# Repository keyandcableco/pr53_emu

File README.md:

# pr53_emu

A replacement display for a Technics SX-PR53 digital piano whose chip-on-glass
LCD died. A tap board sits on the HD44780 bus between the piano's CPU and the
dead display: it mirrors every write, answers the CPU's reads so it never
stalls, logs everything over USB, and forwards each write to a second board
that draws the piano's display on a 3.5" colour TFT. Python tools render the
same display on a laptop and were used to reverse-engineer the glass.

The technique generalizes to most HD44780-compatible LCDs. See
[the writeup](https://keyandcable.com/blog/reviving-the-technics-sx-pr53.html)
for the story and the reasoning behind the design.

```
piano CPU ── HD44780 bus (CN1) ──► carrier J1 ─ level shifters ─► tap (RP2350-Zero) ── USB log ──► tools/
                                                                    │ UART 1 Mbaud
                                                                    ▼
                                                     display (Pico 2) ── 16-bit parallel ──► 3.5" TFT
```

## Status (2026-10-31)

- **Working end to end on the piano.** The carrier board carries both
  RP2350s; the TFT draws the PR53 layout and shows the piano's text.
- **Decoded:** the text lines, tempo, chord root with its flat/sharp,
  transpose, all eight part meters and numbers (hundreds included), and the
  menu page and item readouts with MENU, PAGE, the PAGE arrows and the
  part pointers.
- **Not decoded yet:** chord types and many
  of the shaped labels on the glass (MIDI and more).
  [`docs/front-panel.md`](docs/front-panel.md) tracks the front-panel decode.
- **Carrier v2 works, with one change when you build it:** fit J2 on the
  underside of the board. DB7's pull-down is too weak to do its job on its
  own; the next revision should fix that. Details in
  [`hardware/carrier/README.md`](hardware/carrier/README.md).

## What's in here

| Path | What |
|---|---|
| [`firmware/tap/`](firmware/tap/) | Tap firmware (v18) for the RP2350-Zero: capture, read responses, USB log, display link |
| [`firmware/display/`](firmware/display/) | Display firmware for the Pico 2: decoders, renderer, panel driver, host test |
| [`tools/`](tools/) | Python: live display mock, recorder, offline analyzer, segment-mapping tools |
| [`captures/`](captures/) | Bus recordings from the piano, including the host test's ground-truth frame |
| [`hardware/carrier/`](hardware/carrier/) | The PR53 carrier v2 board: KiCad, generator scripts, Gerbers, bring-up notes (`rev1/` is the first fab) |
| [`hardware/archive/`](hardware/archive/) | Earlier perfboard maps and board plans |
| [`docs/piano-interface.md`](docs/piano-interface.md) | The piano side: CN1 pinout, the bus, busy flag, power |
| [`docs/front-panel.md`](docs/front-panel.md) | Every panel control and display field, decode status, service test modes |

## Build

Needs the [Pico SDK](https://github.com/raspberrypi/pico-sdk) (built with
2.3.0), `arm-none-eabi-gcc`, `cmake` and `make`. Both firmwares find the SDK
through `firmware/pico_sdk_import.cmake`, from `PICO_SDK_PATH` in the
environment or `-DPICO_SDK_PATH=...`.

```bash
export PICO_SDK_PATH=$HOME/pico-sdk
cmake -S firmware/tap     -B build/tap     -DPICO_BOARD=pico2 && make -C build/tap -j
cmake -S firmware/display -B build/display -DPICO_BOARD=pico2 && make -C build/display -j
make -C firmware/display -f host.mk test     # decoder test on the PC, no hardware
```

That gives `build/tap/pr53_emu.uf2` (for the Zero) and
`build/display/pr53_fw.uf2` (for the Pico 2).

## Flash

Hold BOOT (Zero) or BOOTSEL (Pico 2) while plugging in USB, then copy the UF2
onto the RP2350 drive that appears. Power the TFT and the display Pico
together: the display firmware sets up the panel once, at boot.

To check what's already on a board without changing it, use
`picotool verify -f <uf2>` with a picotool built with USB support (see
`hardware/carrier/README.md`, Bring-up).

## Laptop display

```bash
pip install pyserial
python3 tools/pr53_display.py
```

It auto-detects the tap's serial port (override with `--port /dev/ttyACM0` or
`--port COM3`). Power on the piano and you'll see the voice and rhythm names,
the current menu, the raw DDRAM, and a status bar with the event count. If the
log shows `# WARN dropped N events`, the tap's ring buffer overflowed; healthy
runs keep `ring_depth` near 0 on the `# ALIVE` lines. See
[`tools/README.md`](tools/README.md) for the other tools.

## Generalizing to other devices

This trick works on essentially any HD44780-compatible LCD. If you have a piece of vintage gear (synth, drum machine, industrial equipment, arcade board) with a dead text display and the CPU still runs, the same approach applies:

1. Wire the RP2350 to RS, R/W, CS, and DB4-DB7 (through level shifters if the bus is 5 V).
2. Add a pull-down on DB7.
3. Adjust `pio_read_response_init` timing if your target CPU's bus is faster than the SX-PR53's.
4. Rebuild the Python display's LCD dimensions if it's not 16x2.

The state machine and event log format are display-agnostic. The only Technics-specific behavior is the persistent-state heuristic in `pr53_display.py`, which classifies text as menu-label vs voice/rhythm name — easy to strip out or replace.

If you adapt this to another device I'd love to hear about it.

---

## Acknowledgments

Substantial pair-programming with [Claude Opus 4.7](https://www.anthropic.com/claude). The physical work — probing, cutting, wiring, verifying — was mine; the C firmware, the Python tools, the electrical debugging plans, and most of the pattern-matching on byte-level corruption came out of that collaboration. Neither side could have done it alone.

## Related

- [The Key & Cable Company](https://keyandcable.com) — the shop
- [openchord-project](https://github.com/keyandcableco/openchord-project) — earlier RP2350-based restoration for the Suzuki Omnichord OM-27
- [Full writeup](https://keyandcable.com/blog/reviving-the-technics-sx-pr53.html)

## License

MIT. See [LICENSE](LICENSE).

`firmware/pico_sdk_import.cmake` is from the Raspberry Pi Pico SDK and keeps its BSD-3-Clause licence (see the file header).

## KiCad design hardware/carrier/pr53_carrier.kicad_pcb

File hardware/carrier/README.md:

# PR53 Carrier Board (v2)

A 100 x 62 mm 2-layer board that carries the existing two-module build,
socketed on 2.54 mm headers:

    J1 piano in ──► U1/U2 BSS138 shifters ──► A1 RP2350-Zero (tap)
                                                   │ GP8 → GP21 link
                                                   ▼
                              J2 LCD out ◄── A2 Pico 2 (display)

**Status (v2): built and working** (first power-up 2026-10-31, on USB
power). J2 has to be fitted on the underside; see Bring-up below. Routed, DRC 0 errors / 0 unconnected (2
silkscreen-at-edge warnings on A2, same as v1), Gerbers in `gerbers/` and
`pr53_carrier_jlcpcb.zip`. Both module footprints are verified (table below).

**v1 (fabbed 2026-10) has the wrong shifter footprint.** Its rows are 12.70 mm
apart instead of 10.16 mm, and power and GND are swapped on both sides. A
shifter plugged straight into a v1 board is reverse-powered, so jumper LV,
HV and GND by hand. v1 files are kept in `rev1/`.

The back silkscreen carries the maker's mark (The Key & Cable Co. /
keyandcable.com / Technics PR53 Carrier Board) and a QR code to
https://keyandcable.com, drawn as vector squares from
`keyandcable_qr.txt` (0.48 mm modules, 12 mm). It sits between the
Pico's pin rows, inside a via-free zone so no drill hole lands in it.

## Module dimensions

| Module | Value | Source | Constant in `gen_footprints.py` |
|---|---|---|---|
| RP2350-Zero: long edge to long edge, pin centres | 15.24 mm (6 holes) | test-fitted on a v1 board | `ZERO_COL_SPACING` |
| BSS138 4-ch module: HV row to LV row | 10.16 mm (4 holes) | SparkFun's `.brd` | `SHIFTER_ROW_SPACING` |

Shifter pin order, module top view, HV row on the left and LV row on the
right, top to bottom: `HV4 HV3 GND HV HV2 HV1` and `LV4 LV3 GND LV LV2 LV1`.
Taken from SparkFun BOB-12009's own board file
(github.com/sparkfun/Logic_Level_Bidirectional, `Hardware/*.brd`), which the
cheap clones copy.

## Ordering (JLCPCB or similar)

Upload `pr53_carrier_jlcpcb.zip`. 2 layers, 1.6 mm, everything else default.
All traces are ≥ 0.25 mm, vias 0.7/0.35 mm, so nothing needs the expensive options.

## BOM (all through-hole, hand-solder)

| Ref | Part | Note |
|---|---|---|
| A1 | Waveshare RP2350-Zero + 2x 1x9 headers | USB-C at the bottom edge |
| A2 | Raspberry Pi Pico 2 + 2x 1x20 headers | USB at the bottom edge |
| U1, U2 | BSS138 4-ch level shifter module + 2x 1x6 headers each | |
| J1 | 9-pos 3.5 mm screw terminal (Phoenix PT 1,5/9-3.5-H, or 3+3+3 cheap KF350 blocks) | wire openings face the board edge |
| J2 | 2x18 2.54 mm male header | IDC ribbon → panel, pin 1 marked. **Fit it on the underside** (see Bring-up) |
| R1 | 10k axial | **DB7 busy-flag pulldown, needed for the board to work** |
| R2 | 1k axial | power LED |
| D1, D2 | 1N5819 Schottky | 5V into each module (blocks USB back-feed) |
| D3 | 3 mm LED | power |
| C1 | 100 µF 10 V radial, 2.5 mm pitch | |
| C2 | 100 nF ceramic, 5 mm pitch | |

Sockets (female headers) instead of soldering the modules down are a good idea.
The footprints are plain 2.54 mm holes, so either works.

## Wiring (matches the firmware exactly)

**J1, piano in, top to bottom:** GND, +5V, CS, RW, RS, DB7, DB6, DB5, DB4

| Piano | Shifter | Zero |
|---|---|---|
| DB4 | U1 ch1 | GP0 |
| DB5 | U1 ch2 | GP1 |
| DB6 | U1 ch3 | GP2 |
| DB7 (+R1 10k to GND, 5V side) | U1 ch4 | GP3 |
| RS | U2 ch2 | GP4 |
| RW | U2 ch3 | GP5 |
| CS | U2 ch4 | GP7 |
| — | — | GP8 → Pico GP21 (UART link) |

Channels are assigned in the module's own top-to-bottom order, so the
lines run straight across with no crossings. U2 ch1 is spare.

**Shifters are bidirectional on purpose.** The tap firmware answers the
piano's read cycles on DB4-7 (PIO1 in `firmware/tap/src/pr53_emu.c`). A one-way
buffer such as the 74LVC245 in `../archive/KICAD_NETLIST.md` would break that.

**J2, LCD out:** numbered 1:1 with the HiLetgo 36-pin header (straight-through
ribbon). Pico GP0-15 → DB0-15, GP16 RS, GP17 WR, GP18 RST, CS (pin 21) tied
to GND, 5V on pins 1-2, GND on 35-36.

**Power:** one +5V rail from the piano (J1). It feeds the shifter HV sides
and the LCD directly, and each module through its own Schottky (Zero 5V pin,
Pico VSYS). You can plug USB into either module for reflashing while the
piano is on. The shifter LV side runs from the Zero's 3V3 pin, which is the
same rail as the GPIOs it talks to.

## Rebuilding

Everything is generated, so edit the scripts rather than the board:

```bash
/usr/bin/python3 gen_footprints.py      # pr53.pretty (Zero + shifter footprints)
/usr/bin/python3 gen_board.py           # placement, nets, rules, pours (unrouted)
/usr/bin/python3 route.py freerouting-1.9.0.jar   # autoroute + GND stitching (~1 min)
kicad-cli pcb drc pr53_carrier.kicad_pcb
```

Then re-export the Gerbers (or File → Fabrication Outputs in KiCad).
Freerouting 1.9.0 is the last release that runs on Java 17:
https://github.com/freerouting/freerouting/releases/tag/v1.9.0

Use KiCad's own python (`/usr/bin/python3`), the one that can `import pcbnew`.
Re-running `gen_board.py` discards the routing, so route last. Hand edits in
KiCad are fine once you stop regenerating.

## Bring-up (2026-10-31)

First power-up on the piano. The whole chain works: the piano's LCD writes
reach the tap, cross the GP8 → GP21 link, and the display Pico draws them on
the HiLetgo panel. What it took:

- **J2 goes on the underside.** The panel's 36-pin header comes out of its
  back, so a standard 2x18 IDC ribbon from a top-side J2 lands each odd pin on
  its even neighbour. Power survives (pins 1/2 are both 5V, 35/36 both GND), so
  the backlight comes on, but the panel's RST lands on J2 pin 21 (GND) and the
  panel stays in reset: backlight, blank screen. With J2 on the underside both
  ends plug on from the back and the ribbon is pin for pin. Next revision:
  mirror J2's pin order or put it on the bottom layer.
- **The display Pico sets up the panel once, at boot.** Power the panel and the
  Pico together. A panel connected after the Pico started stays blank until the
  Pico restarts.
- **Piano 5V.** CN1 pin 2 (+5IP) is the piano's +5D through IP101, an ICP-N10
  0.4 A IC protector that also feeds the front-panel boards. On this piano
  IP101 was open (about 2.1 kΩ in circuit, 5 V on one leg and 3 V on the
  other), so pin 2 sagged under any load. The carrier ran from the Zero's USB
  instead, with D1 bridged and J1 +5V disconnected from the piano. Never bridge
  D1 while J1 +5V is connected to the piano: USB would feed the piano's rail.
  Replacement: ICP-N10 or NTE15020E. The carrier's own current draw hasn't been
  measured; check it before putting it on the same 0.4 A protector as the
  front panel.
- **CN1 pinout** (service manual p. 50, MAIN(CPU) CIRCUIT): 1 GND, 2 +5IP,
  3 V0, 4 RS, 5 R/W, 6 CS, 7-14 DB0-DB7. The schematic ties DB0-DB2 to GND and
  leaves DB3 open. Measured: pins 1, 7 and 8 are continuous with the ground foil.
- **DB7 pull-down.** Each shifter module has its own 10k pull-up on the HV
  side, so R1 (10k) only holds DB7 at about half the 5V rail when nothing
  drives it, not a clean low. It works because the tap answers every busy
  check (from tap v18 with all zeros, so busy always reads clear; it also
  starts answering at once instead of after a 3 s wait for USB). Next
  revision: a stronger R1 (or lift the module's DB7 pull-up), so DB7 reads
  low even if a read goes unanswered.
- **First start with the front panel unpowered**, the piano wrote "ALL INITIAL"
  then "ConcertGrand", so it probably reset its settings to factory defaults
  (the August capture started on "Pop Grand").
- **Checking a board's firmware:** the picotool in the SDK build folders has no
  USB support. Build one with `libusb-1.0-dev` installed. If it can't open the
  device, install Raspberry Pi's udev rule for picotool or run it with `sudo`.
  `picotool verify -f <uf2>` compares the flash with a build without writing
  anything.

## Not done

- No schematic. The nets live in `gen_board.py` and the board is the source of
  truth. For a pure module carrier that's fine; ask if you want a `.kicad_sch`.
- No 3D models for the modules, so the 3D view shows bare footprints.

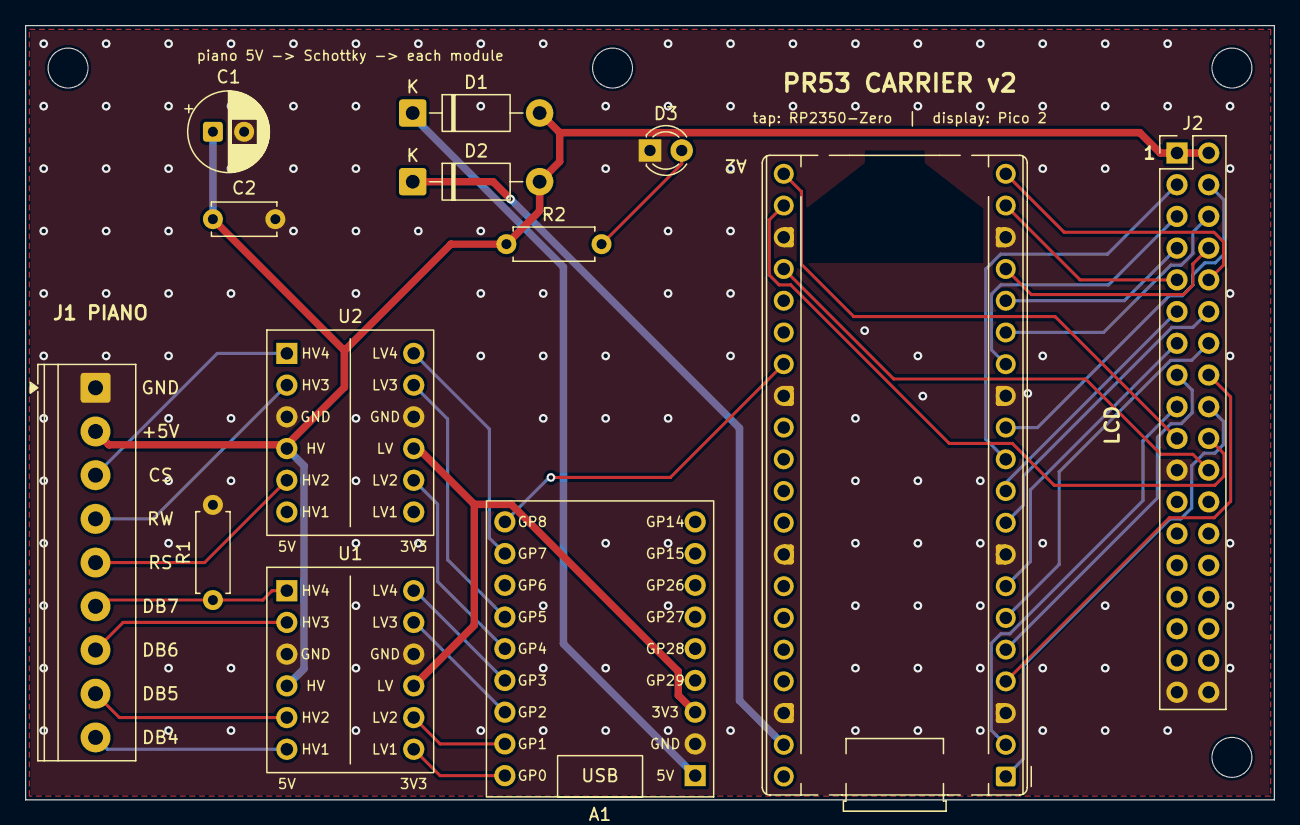
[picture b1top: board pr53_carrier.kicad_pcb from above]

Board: 2 copper layers, 100.0 x 62.0 mm, 17 parts (0 on the bottom side), 40 nets.

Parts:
A1: RP2350-Zero (tap); RP2350-Zero_Socket
A2: Pico 2 (display); RaspberryPi_Pico_Common_THT
C1: 100u 10V; CP_Radial_D6.3mm_P2.50mm
C2: 100n; C_Disc_D5.0mm_W2.5mm_P5.00mm
D1, D2: 1N5819; D_DO-41_SOD81_P10.16mm_Horizontal
D3: PWR; LED_D3.0mm
H1, H2, H3, H4: M3; MountingHole_3.2mm_M3
J1: PR53_IN; TerminalBlock_Phoenix_PT-1,5-9-3.5-H_1x09_P3.50mm_Horizontal
J2: LCD_OUT (HiLetgo 36p); PinHeader_2x18_P2.54mm_Vertical
R1: 10k; R_Axial_DIN0207_L6.3mm_D2.5mm_P7.62mm_Horizontal
R2: 1k; R_Axial_DIN0207_L6.3mm_D2.5mm_P7.62mm_Horizontal
U1: BSS138_4ch (DB4-7); BSS138_4ch_Module
U2: BSS138_4ch (RS/RW/CS); BSS138_4ch_Module

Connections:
+3V3_TAP: A1.3, U1.4, U2.4
+5V: C1.1, C2.1, D1.2, D2.2, J1.2, J2.1, J2.2, R2.1, U1.10, U2.10
+5V_DISP: A2.39, D2.1
+5V_TAP: A1.1, D1.1
CS: J1.3, U2.7
DB4: J1.9, U1.12
DB5: J1.8, U1.11
DB6: J1.7, U1.8
DB7: J1.6, R1.1, U1.7
GND: A1.2, A2.3, A2.8, A2.13, A2.18, A2.23, A2.28, A2.33, A2.38, C1.2, C2.2, D3.1, J1.1, J2.21, J2.35, J2.36, R1.2, U1.3, U1.9, U2.3, U2.9
LCD_DB0: A2.1, J2.18
LCD_DB1: A2.2, J2.17
LCD_DB2: A2.4, J2.16
LCD_DB3: A2.5, J2.15
LCD_DB4: A2.6, J2.14
LCD_DB5: A2.7, J2.13
LCD_DB6: A2.9, J2.12
LCD_DB7: A2.10, J2.11
LCD_DB8: A2.11, J2.3
LCD_DB9: A2.12, J2.4
LCD_DB10: A2.14, J2.5
LCD_DB11: A2.15, J2.6
LCD_DB12: A2.16, J2.7
LCD_DB13: A2.17, J2.8
LCD_DB14: A2.19, J2.9
LCD_DB15: A2.20, J2.10
LCD_RS: A2.21, J2.19
LCD_RST: A2.24, J2.22
LCD_WR: A2.22, J2.20
LED_A: D3.2, R2.2
LINK: A1.18, A2.27
RS: J1.5, U2.11
RW: J1.4, U2.8
T_CS: A1.17, U2.1
T_DB4: A1.10, U1.6
T_DB5: A1.11, U1.5
T_DB6: A1.12, U1.2
T_DB7: A1.13, U1.1
T_RS: A1.14, U2.5
T_RW: A1.15, U2.2
